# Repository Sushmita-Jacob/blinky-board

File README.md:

# blinky-board
Blinky Board is a starter project for Hack Club's Stasis program. I designed this LED chaser in KiCad in 3.1 hours. I created a schematic, footprint, and PCB and learned how to connect parts using wires. My PCB is shaped like a lightbulb with LEDs lighting up in its outer arc. The other components are in the middle and bottom of the lightbulb shape.

# Journal #1: NE555P and 4017 Connections

***April 5, 2026: 1.3 hours***

I'm almost done with the schematic for Blinky Board. First I laid out all the components listed. I connected the header to 5V and GND. Then, I connected the NE555P to capacitors, resistors, and a potentiometer. Finally I wired the 4017 IC to all 10 of my LEDs and the NE555P.

The hardest part was figuring out how KiCad functioned since it was my first time using it. It took longer than I'd like to admit to figure out how to connect something to 5V and GND (the power symbols were in the same place as the components) and where the labels were. However, everything else was pretty easy! Skimming the rest of the article, my next steps are adding a footprint and making a PCB.

# Journal #2: Footprints and PCB

***April 13, 2026: 1.75 hours***

I had trouble figuring out how to add footprints to my schematic. However, I noticed that on the top bar of the schematic, there is a Footprint Editor button. The Blinky Board tutorial seemed to have the intention of including a screenshot of the footprints but got cut out or removed. I searched through messages in the Hack Club Slack to find the right footprints that will match with the components mailed in the Blinky Board kit.

Then, I updated the PCB based on the schematic and wired all the components together. I used vias for multiple connections to avoid colliding different colors. I noticed that for some connections, the ratlines did not go away even after the components had a wire between them, but I realized they were still connected regardless after using the Design Rules Checker. Finally, I personalized my board by making it into the shape of a light bulb using Edge.Cuts. I added a heart and star in the middle as well on the front and back of the silkscreen.

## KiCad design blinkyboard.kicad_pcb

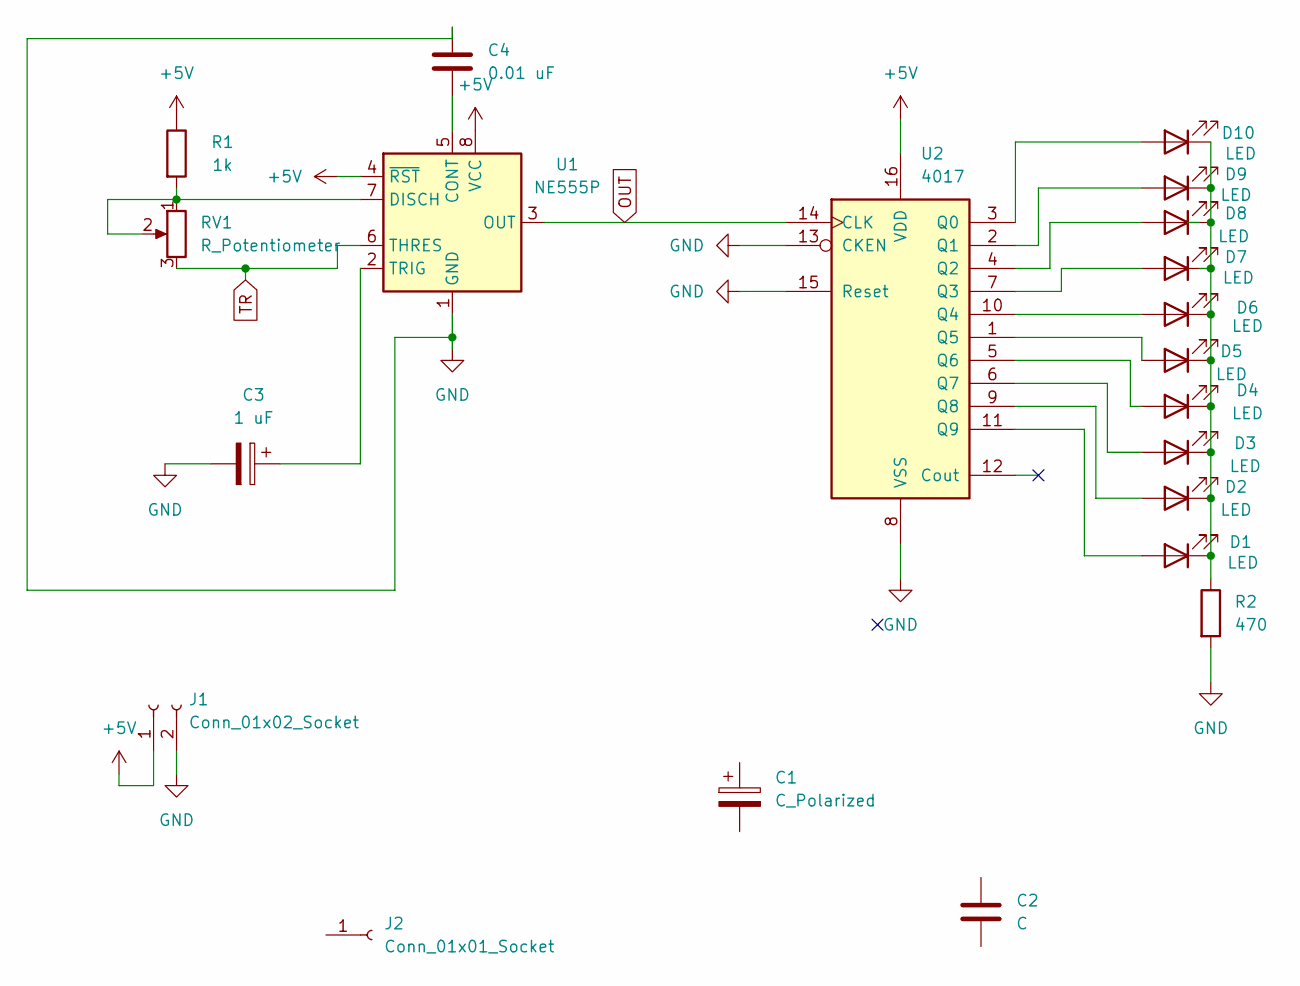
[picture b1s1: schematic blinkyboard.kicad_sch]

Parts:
C1: C_Polarized; C_Radial_D5.0mm_H5.0mm_P2.00mm
C2: C; C_Radial_D5.0mm_H5.0mm_P2.00mm
C3: 1 uF; C_Radial_D5.0mm_H5.0mm_P2.00mm
C4: 0.01 uF; C_Radial_D5.0mm_H5.0mm_P2.00mm
D1, D2, D3, D4, D5, D6, D7, D8, D9, D10: LED; LED_D3.0mm
J1: Conn_01x02_Socket; PinSocket_1x02_P2.54mm_Vertical
J2: Conn_01x01_Socket; PinSocket_1x01_P2.54mm_Vertical
R1: 1k; R_Axial_DIN0207_L6.3mm_D2.5mm_P7.62mm_Horizontal
R2: 470; R_Axial_DIN0207_L6.3mm_D2.5mm_P7.62mm_Horizontal
RV1: R_Potentiometer; Potentiometer_Vishay_T93YA_Vertical
U1: NE555P; DIP-8_W7.62mm
U2: 4017; N16

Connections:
+5V: J1.1, R1.1, U1.4 (~RST), U1.8 (VCC), U2.16 (VDD)
GND: C3.2, C4.1, J1.2, R2.2, U1.1 (GND), U2.8 (VSS), U2.13 (CKEN), U2.15 (Reset)
unnamed: D1.2 (A), U2.11 (Q9)
unnamed: D1.1 (K), D2.1 (K), D3.1 (K), D4.1 (K), D5.1 (K), D6.1 (K), D7.1 (K), D8.1 (K), D9.1 (K), D10.1 (K), R2.1
unnamed: D2.2 (A), U2.9 (Q8)
unnamed: D3.2 (A), U2.6 (Q7)
unnamed: D4.2 (A), U2.5 (Q6)
unnamed: D5.2 (A), U2.1 (Q5)
unnamed: D6.2 (A), U2.10 (Q4)
unnamed: D7.2 (A), U2.7 (Q3)
unnamed: D8.2 (A), U2.4 (Q2)
unnamed: D9.2 (A), U2.2 (Q1)
unnamed: D10.2 (A), U2.3 (Q0)
unnamed: C4.2, U1.5 (CONT)
unnamed: R1.2, RV1.1, RV1.2, U1.7 (DISCH)
unnamed: C3.1, U1.2 (TRIG)
OUT: U1.3 (OUT), U2.14 (CLK)
TR: RV1.3, U1.6 (THRES)

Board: 2 copper layers, 21 parts (0 on the bottom side), 18 nets, no tracks yet.
